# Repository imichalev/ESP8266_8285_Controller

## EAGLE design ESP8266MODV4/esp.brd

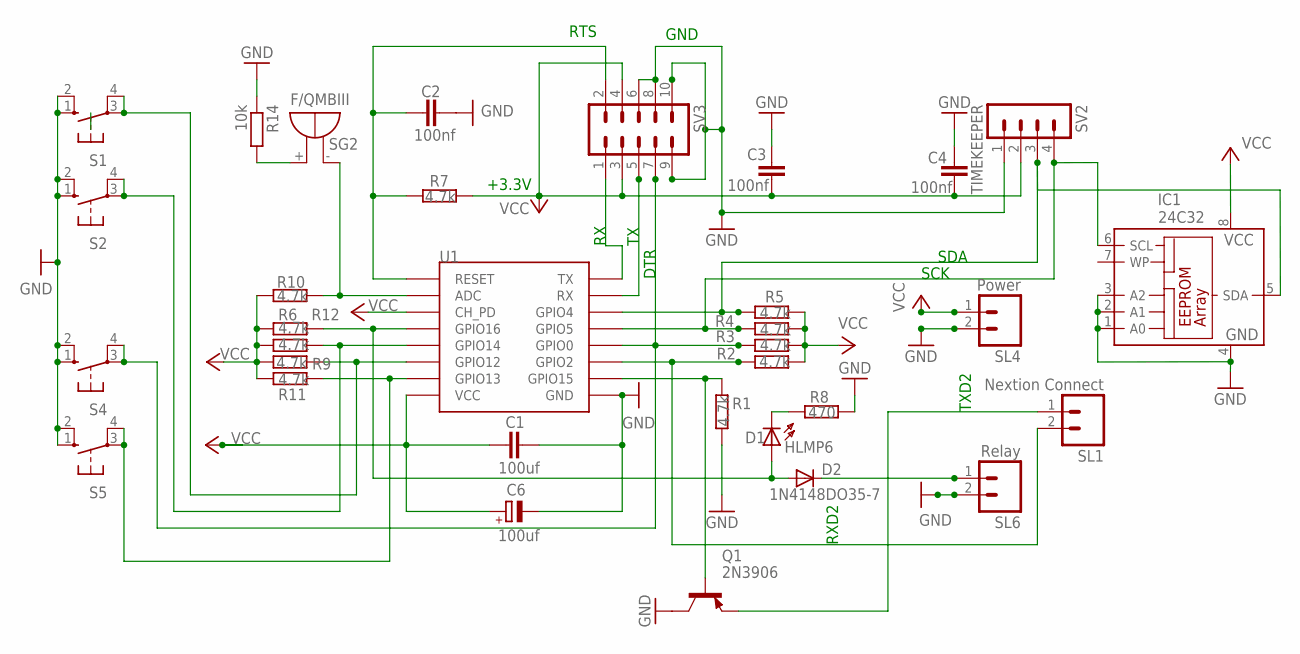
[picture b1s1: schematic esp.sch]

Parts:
C1: 100uf; C0805
C2, C3, C4: 100nf; C0805
C6: 100uf; E5-10,5
D1: HLMP6
D2: 1N4148DO35-7; DO35-7
IC1: 24C32; SO-08
Q1: 2N3906; TO92
R1, R2, R3, R4, R5, R6, R7, R9, R10, R11, R12: 4.7k; R0805
R8: 470; R0805
R14: 10k; R0805
S1, S2, S4, S5: 10-XX; B3F-10XX
SG2: F/QMBIII
SL1: Nextion Connect; 02P
SL4: Power; 02P
SL6: Relay; 02P
SV2: TIMEKEEPER; MA04-1
SV3: MA05-2
U1: ESP12SMD; ESP12-SMD

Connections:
ADC: R10.2, SG2.- (+), U1.ADC
DTR: R3.1, S4.3, S4.4 (P1), SV3.7, U1.GPIO0
GND: C1.1, C2.1, C3.2, C4.2, C6.-, IC1.1 (A0), IC1.2 (A1), IC1.3 (A2), IC1.4 (GND), Q1.1 (C), R1.1, R8.1, R14.1, S1.1 (S), S1.2 (S1), S2.1 (S), S2.2 (S1), S4.1 (S), S4.2 (S1), S5.1 (S), S5.2 (S1), SL4.2, SL6.2, SV2.1, SV3.6, SV3.8, SV3.9, SV3.10, U1.GND
GPIO02: R11.2, S5.3, S5.4 (P1), U1.GPIO13
GPIO12: R9.2, S1.3, S1.4 (P1), U1.GPIO12
GPIO14: R12.2, S2.3, S2.4 (P1), U1.GPIO14
GPIO15: Q1.2 (B), R1.2, U1.GPIO15
GPIO16: D1.A, D2.A, R6.2, U1.GPIO16
unnamed: D2.C, SL6.1
unnamed: Q1.3 (E), SL1.1
unnamed: R14.2, SG2.+ (-)
unnamed: D1.K, R8.2
RTS: C2.2, R7.2, SV3.2, U1.RESET
RX: SV3.1, U1.TXD0 (TX)
RXD2: R2.1, SL1.2, U1.GPIO2
SCK: IC1.6 (SCL), R4.1, SV2.4, U1.GPIO5
SDA: IC1.5 (SDA), R5.1, SV2.3, U1.GPIO4
TX: SV3.5, U1.RXD0 (RX)
VCC: C1.2, C3.1, C4.1, C6.+, IC1.8 (VCC), R2.2, R3.2, R4.2, R5.2, R6.1, R7.1, R9.1, R10.1, R11.1, R12.1, SL4.1, SV2.2, SV3.3, SV3.4, U1.CH_PD, U1.VCC

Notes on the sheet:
+3.3V
GND
DTR
RTS
SDA
SCK
RXD2
TXD2

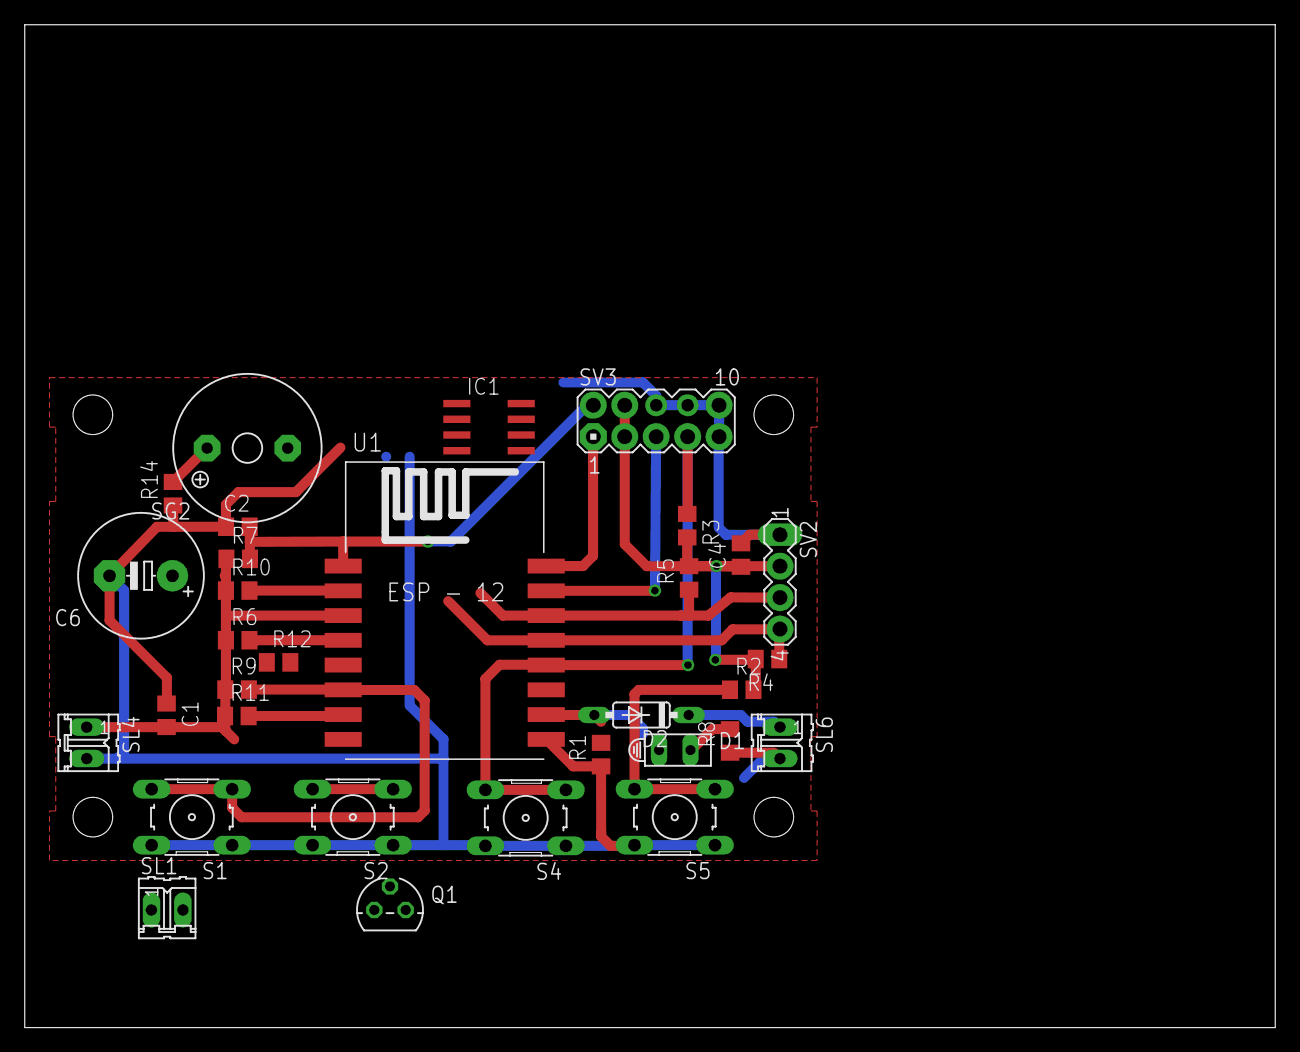
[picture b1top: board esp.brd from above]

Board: 2 copper layers, 101.0 x 81.0 mm, 33 parts (1 on the bottom side), 19 nets.

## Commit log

2018-12-03 StartProject
2018-12-03 Next Code
2018-12-21 Start Project
2018-12-21 add Nextion Display
2018-12-22 add Nextion.h
2018-12-25 Nection Library
2018-12-27 Nextion Display
2018-12-29 Add si7021
2018-12-30 si7021 add floatToString
2018-12-31 Add humidity and new HMI
2018-12-31 add ,gitignore
2019-01-01 checking
2019-01-05 Add mqqt topic /data/jsn
2019-01-06 modify json
2019-01-08 add float for Humidity
2019-01-17 add pcb
2019-01-18 resolve power blinking
2019-01-19 add year month date
2019-01-20 thermocontroller
